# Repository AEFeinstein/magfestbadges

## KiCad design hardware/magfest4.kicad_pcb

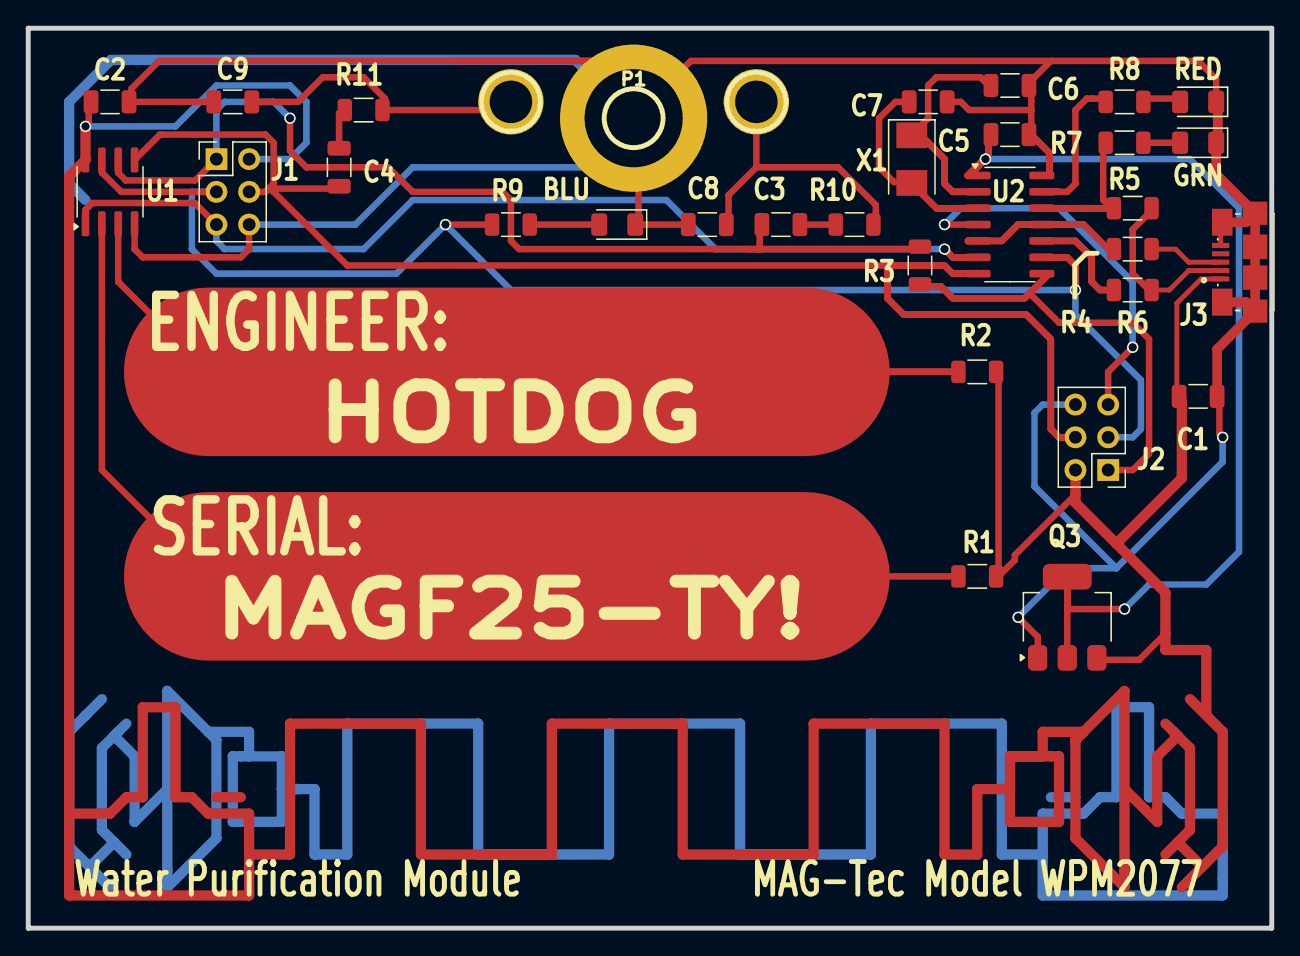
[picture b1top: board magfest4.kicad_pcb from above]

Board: 2 copper layers, 96.5 x 69.8 mm, 33 parts (0 on the bottom side), 26 nets.

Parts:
C1, C3, C4: 10u; C_1206_3216Metric
C2: .1u; C_1206_3216Metric
C5: 1u; C_1206_3216Metric
C6, C7: 12p; C_1206_3216Metric
C8, C9: .022u; C_1206_3216Metric
D1: GRN; D_1206_3216Metric
D2: RED; D_1206_3216Metric
D3: LED; D_1206_3216Metric
J1, J2: AVR-ISP-6; PinHeader_2x03_P2.54mm_Vertical
J3: USB_B_Micro; AMPHENOL_10118192-0001LF
P1, P6, P7: CONN_1; 1pin
Q3: AP1117; SOT-223-3_TabPin2
R1, R2: 1M; R_1206_3216Metric
R3: 120; R_1206_3216Metric
R4, R6: 33; R_1206_3216Metric
R5: 1k5; R_1206_3216Metric
R7, R8, R9: 680; R_1206_3216Metric
R10, R11: 1k; R_1206_3216Metric
U1: ATTINY25-45-85/DIP-SO; SOIC-8_3.9x4.9mm_P1.27mm
U2: ATTINY24-44-84/DIP-SO; SOIC-14_3.9x8.7mm_P1.27mm
X1: QUARTZCMS4; Crystal_SMD_5032-2Pin_5.0x3.2mm

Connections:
/85RESET: J1.5 (~RST), U1.1 (~RESET/PB5), U2.6 (PA7)
/MISO: C3.2, J1.1 (MISO), R3.1, U1.6 (PB1)
/MISO_PGM: J2.1 (MISO), R3.2, U2.8 (PA5)
/MOSI: C4.2, J1.4 (MOSI), J2.4 (MOSI), U1.5 (AREF/PB0), U2.7 (PA6)
/PGM_ACTIVE: R8.1, U2.13 (AREF/PA0)
/PGM_ON: R5.1, R7.1, U2.12 (PA1)
/SCK: J1.3 (SCK), J2.3 (SCK), R9.1, U1.7 (PB2), U2.9 (PA4)
/Touch1: R2.2, U1.3 (XTAL2/PB4)
/Touch2: R1.2, U1.2 (XTAL1/PB3)
GND: C1.2, C2.2, C5.2, C6.1, C7.1, C8.2, C9.2, D1.1 (K), D2.1 (K), D3.1 (K), J1.6 (GND), J2.6 (GND), J3.5 (GND), J3.6 (Shield), P1.1, Q3.1 (GND), U1.4 (GND), U2.14 (GND)
unnamed: C3.1, R10.2
unnamed: C4.1, R11.2
unnamed: C8.1, P6.1, R10.1
unnamed: C9.1, P7.1, R11.1
unnamed: D1.2 (A), R7.2
unnamed: D2.2 (A), R8.2
unnamed: D3.2 (A), R9.2
unnamed: J2.5 (~RST), U2.4 (~RESET/PB3)
unnamed: J3.3 (D+), R4.2
unnamed: J3.2 (D-), R5.2, R6.2
unnamed: C5.1, Q3.2 (VO), U2.1 (VCC)
unnamed: R4.1, U2.5 (PB2), U2.11 (PA2)
unnamed: R6.1, U2.10 (PA3)
unnamed: C6.2, U2.2 (XTAL1/PB0), X1.1
unnamed: C7.2, U2.3 (XTAL2/PB1), X1.2
VCC: C1.1, C2.1, J1.2 (VCC), J2.2 (VCC), J3.1 (VBUS), Q3.3 (VI), R1.1, R2.1, U1.8 (VCC)

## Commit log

2024-12-30 Attempt to modernize the water chip TODO: fix xtal, fix USB, validate MCU footprints
2024-12-30 Update PCB text
2024-12-30 Added LSCS parts
2024-12-31 Fix parts for JLCPCB
